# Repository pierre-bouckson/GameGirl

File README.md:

# GameGirl

## Intro
I create this gamegirl for my nieces & for my personnal pleasure

## What

## Game

- pong
- snake
- 2048
- tetris
- rocket
- puissance 4
- casse briques
- demineur
- morpion
- space invaders

## Features

- STM32F429ZIT6
- 2.4" QVGA TFT LCD 
- Joystick
- 2 button 
- 1 start button
- 1 buzzer
- EPROM (see if that neccesary)
- 3D printed case
- Lithium-ion
- USB type C charge 

## Display pipeline

The framebuffer (240×320, RGB565, 150 KB) lives in the external SDRAM at `0xD0000000` (FMC bank 2).

```
          writes                        reads (DMA)
  CPU  ────────────►  SDRAM  ◄────────────  LTDC  ──── parallel RGB ───►  ILI9341
                  (0xD0000000)                        (pixels, ~60 Hz)    (screen)
        via FMC                via FMC
                                            SPI5 ──── config only ─────►  ILI9341
```

- **CPU** draws pixels into the framebuffer in SDRAM, through the FMC.
- **LTDC** has its own DMA: it continuously reads the SDRAM line by line, with no CPU involvement.
- It pushes the pixels to the screen over the **parallel RGB bus** (R/G/B, HSYNC, VSYNC, DOTCLK).
- **ILI9341** just displays what it receives; it never reads memory itself.
- **SPI5** is only used once in `ili9341_Init()` to configure the panel (RGB mode, orientation…). No pixel goes through it.

CPU and LTDC share the FMC bandwidth. The LTDC needs about 9 MB/s (240 × 320 × 2 bytes × 60 Hz) out of ~128 MB/s theoretical (16-bit SDRAM @ 64 MHz), so plenty is left for the CPU.

Because the LTDC reads continuously while the CPU writes into the same buffer, a single buffer can cause tearing. The SDRAM leaves room for double buffering (2 × 150 KB).

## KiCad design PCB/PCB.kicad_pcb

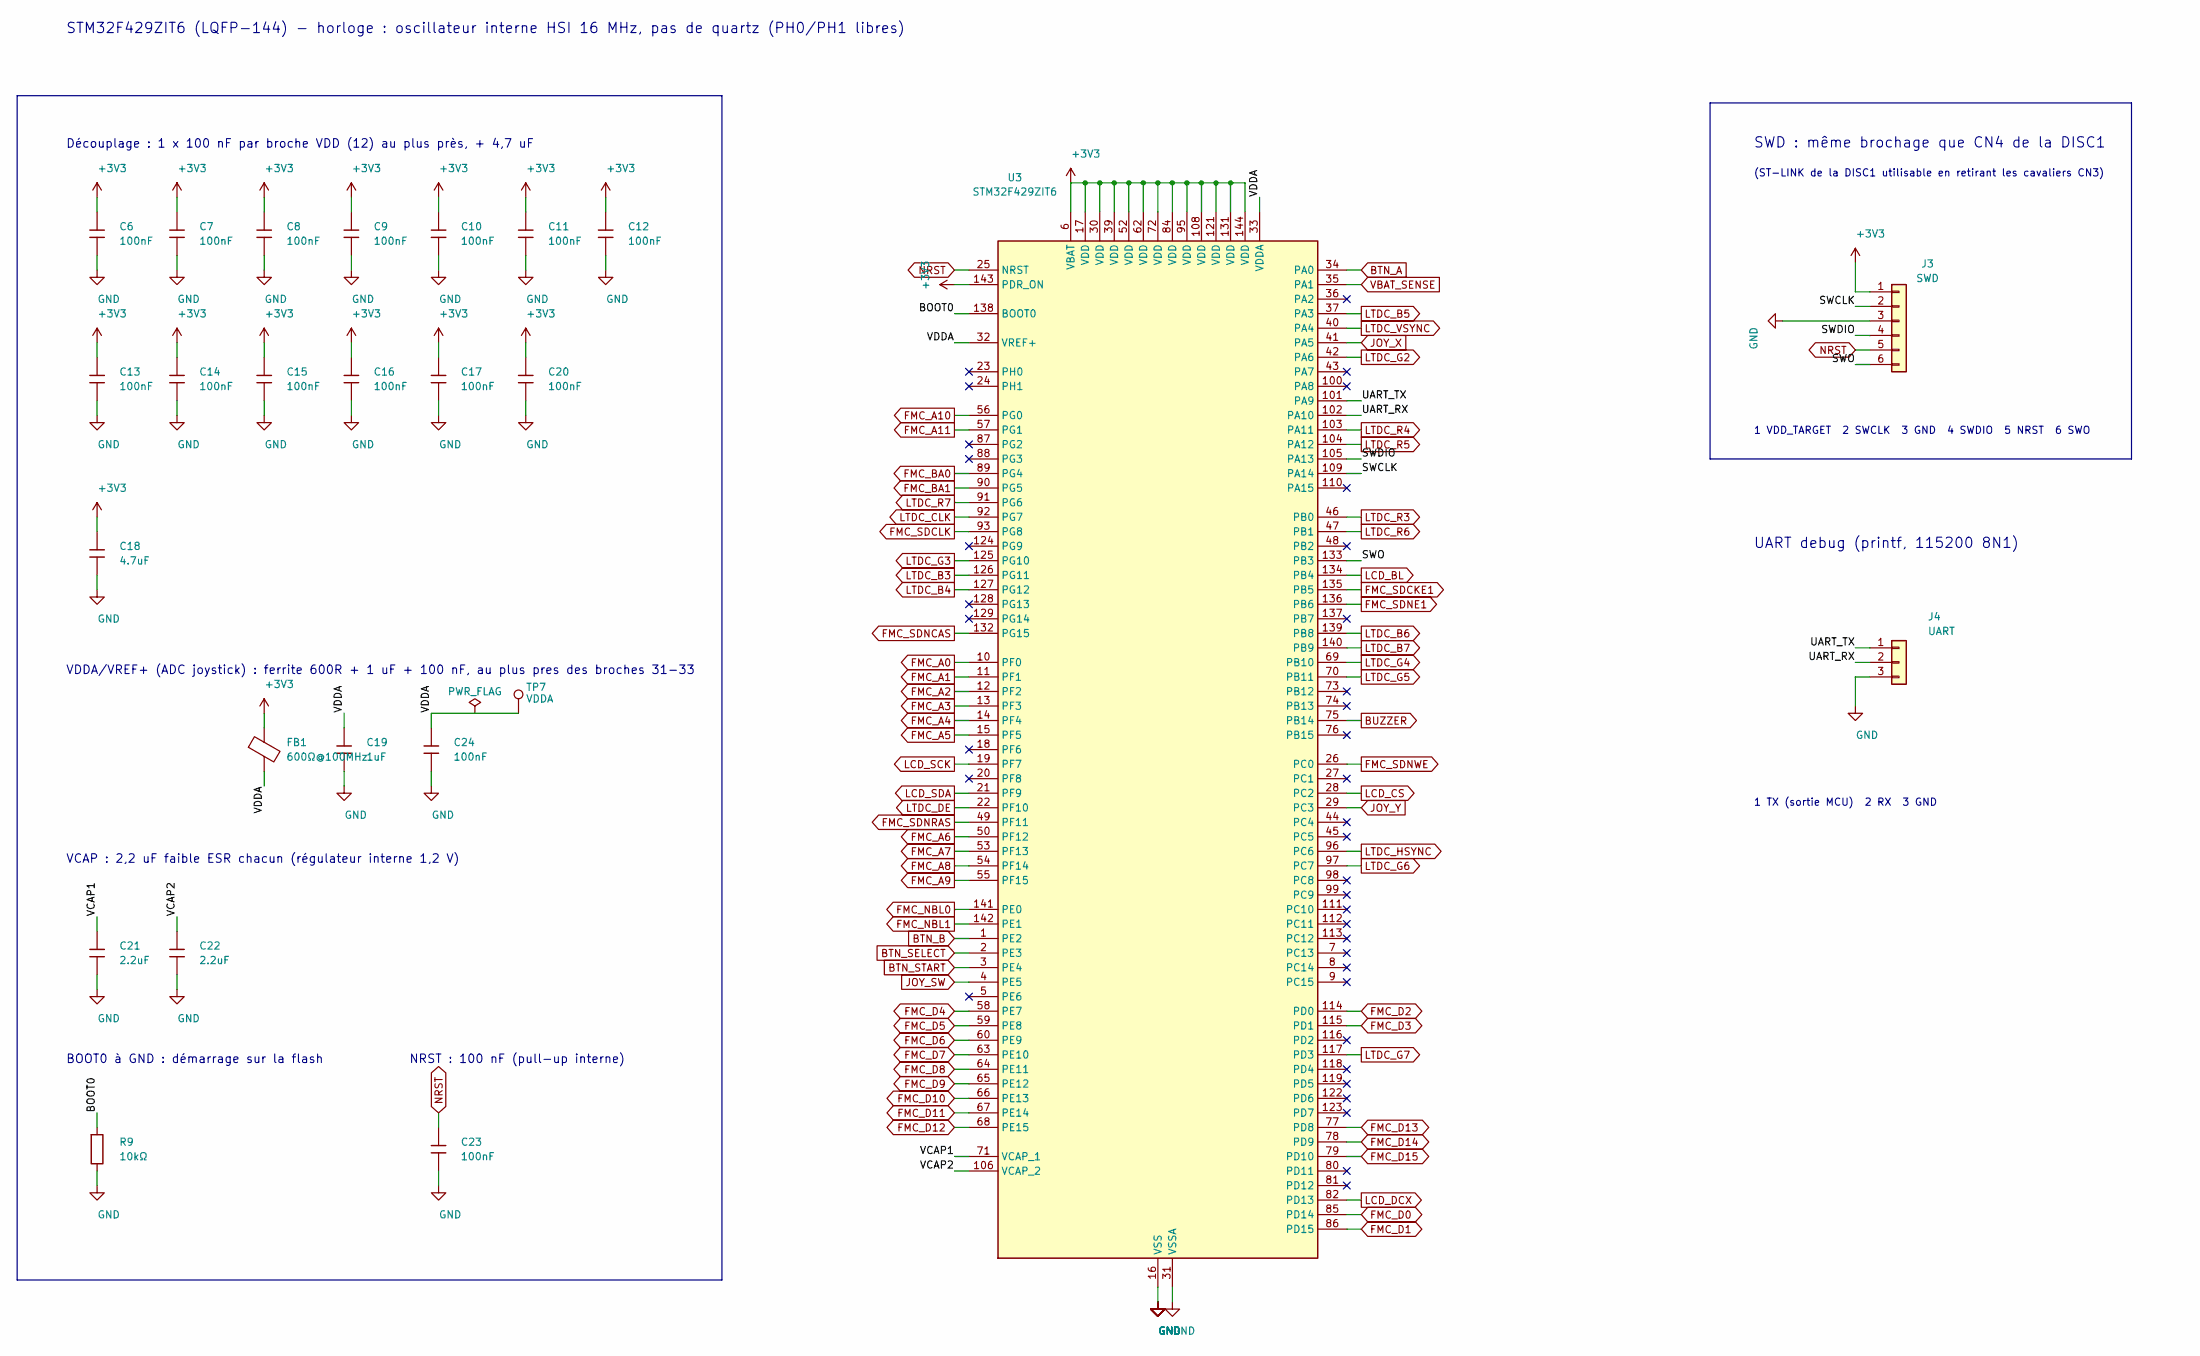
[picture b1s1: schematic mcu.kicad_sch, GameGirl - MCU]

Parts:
C6, C7, C8, C9, C10, C11, C12, C13, C14, C15, C16, C17, C20, C23, C24: 100nF; C_0402; LCSC C1525
C18: 4.7uF; C_0603; LCSC C19666
C19: 1uF; C_0603; LCSC C15849
C21, C22: 2.2uF; C_0603; LCSC C23630
FB1: 600Ω@100MHz; FB_0603; LCSC C1002
J3: SWD; PinHeader_1x06_P2.54mm_Vertical
J4: UART; PinHeader_1x03_P2.54mm_Vertical
R9: 10kΩ; R_0402; LCSC C25744
TP7: VDDA; TestPoint_Pad_D1.5mm
U3: STM32F429ZIT6; LQFP-144_20x20mm_P0.5mm; LCSC C84808

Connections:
+3V3: C6.1, C7.1, C8.1, C9.1, C10.1, C11.1, C12.1, C13.1, C14.1, C15.1, C16.1, C17.1, C18.1, C20.1, FB1.1, J3.1, U3.6 (VBAT), U3.17 (VDD), U3.30 (VDD), U3.39 (VDD), U3.52 (VDD), U3.62 (VDD), U3.72 (VDD), U3.84 (VDD), U3.95 (VDD), U3.108 (VDD), U3.121 (VDD), U3.131 (VDD), U3.143 (PDR_ON), U3.144 (VDD); also elsewhere on the board
/MCU/BOOT0: R9.1, U3.138 (BOOT0)
/MCU/SWCLK: J3.2, U3.109 (PA14)
/MCU/SWDIO: J3.4, U3.105 (PA13)
/MCU/SWO: J3.6, U3.133 (PB3)
/MCU/UART_RX: J4.2, U3.102 (PA10)
/MCU/UART_TX: J4.1, U3.101 (PA9)
/MCU/VCAP1: C21.1, U3.71 (VCAP_1)
/MCU/VCAP2: C22.1, U3.106 (VCAP_2)
/MCU/VDDA: C19.1, C24.1, FB1.2, TP7.1, U3.32 (VREF+), U3.33 (VDDA)
BTN_A: U3.34 (PA0); also elsewhere on the board
BTN_B: U3.1 (PE2); also elsewhere on the board
BTN_SELECT: U3.2 (PE3); also elsewhere on the board
BTN_START: U3.3 (PE4); also elsewhere on the board
BUZZER: U3.75 (PB14); also elsewhere on the board
FMC_A0: U3.10 (PF0); also elsewhere on the board
FMC_A1: U3.11 (PF1); also elsewhere on the board
FMC_A2: U3.12 (PF2); also elsewhere on the board
FMC_A3: U3.13 (PF3); also elsewhere on the board
FMC_A4: U3.14 (PF4); also elsewhere on the board
FMC_A5: U3.15 (PF5); also elsewhere on the board
FMC_A6: U3.50 (PF12); also elsewhere on the board
FMC_A7: U3.53 (PF13); also elsewhere on the board
FMC_A8: U3.54 (PF14); also elsewhere on the board
FMC_A9: U3.55 (PF15); also elsewhere on the board
FMC_A10: U3.56 (PG0); also elsewhere on the board
FMC_A11: U3.57 (PG1); also elsewhere on the board
FMC_BA0: U3.89 (PG4); also elsewhere on the board
FMC_BA1: U3.90 (PG5); also elsewhere on the board
FMC_D0: U3.85 (PD14); also elsewhere on the board
FMC_D1: U3.86 (PD15); also elsewhere on the board
FMC_D2: U3.114 (PD0); also elsewhere on the board
FMC_D3: U3.115 (PD1); also elsewhere on the board
FMC_D4: U3.58 (PE7); also elsewhere on the board
FMC_D5: U3.59 (PE8); also elsewhere on the board
FMC_D6: U3.60 (PE9); also elsewhere on the board
FMC_D7: U3.63 (PE10); also elsewhere on the board
FMC_D8: U3.64 (PE11); also elsewhere on the board
FMC_D9: U3.65 (PE12); also elsewhere on the board
FMC_D10: U3.66 (PE13); also elsewhere on the board
FMC_D11: U3.67 (PE14); also elsewhere on the board
FMC_D12: U3.68 (PE15); also elsewhere on the board
FMC_D13: U3.77 (PD8); also elsewhere on the board
FMC_D14: U3.78 (PD9); also elsewhere on the board
FMC_D15: U3.79 (PD10); also elsewhere on the board
FMC_NBL0: U3.141 (PE0); also elsewhere on the board
FMC_NBL1: U3.142 (PE1); also elsewhere on the board
FMC_SDCKE1: U3.135 (PB5); also elsewhere on the board
FMC_SDCLK: U3.93 (PG8); also elsewhere on the board
FMC_SDNCAS: U3.132 (PG15); also elsewhere on the board
FMC_SDNE1: U3.136 (PB6); also elsewhere on the board
FMC_SDNRAS: U3.49 (PF11); also elsewhere on the board
FMC_SDNWE: U3.26 (PC0); also elsewhere on the board
GND: C6.2, C7.2, C8.2, C9.2, C10.2, C11.2, C12.2, C13.2, C14.2, C15.2, C16.2, C17.2, C18.2, C19.2, C20.2, C21.2, C22.2, C23.2, C24.2, J3.3, J4.3, R9.2, U3.16 (VSS), U3.31 (VSSA), U3.38 (VSS), U3.51 (VSS), U3.61 (VSS), U3.83 (VSS), U3.94 (VSS), U3.107 (VSS), U3.120 (VSS), U3.130 (VSS); also elsewhere on the board
JOY_SW: U3.4 (PE5); also elsewhere on the board
JOY_X: U3.41 (PA5); also elsewhere on the board
JOY_Y: U3.29 (PC3); also elsewhere on the board
LCD_BL: U3.134 (PB4); also elsewhere on the board
LCD_CS: U3.28 (PC2); also elsewhere on the board
LCD_DCX: U3.82 (PD13); also elsewhere on the board
LCD_SCK: U3.19 (PF7); also elsewhere on the board
LCD_SDA: U3.21 (PF9); also elsewhere on the board
LTDC_B3: U3.126 (PG11); also elsewhere on the board
LTDC_B4: U3.127 (PG12); also elsewhere on the board
LTDC_B5: U3.37 (PA3); also elsewhere on the board
LTDC_B6: U3.139 (PB8); also elsewhere on the board
LTDC_B7: U3.140 (PB9); also elsewhere on the board
LTDC_CLK: U3.92 (PG7); also elsewhere on the board
LTDC_DE: U3.22 (PF10); also elsewhere on the board
LTDC_G2: U3.42 (PA6); also elsewhere on the board
LTDC_G3: U3.125 (PG10); also elsewhere on the board
LTDC_G4: U3.69 (PB10); also elsewhere on the board
LTDC_G5: U3.70 (PB11); also elsewhere on the board
LTDC_G6: U3.97 (PC7); also elsewhere on the board
LTDC_G7: U3.117 (PD3); also elsewhere on the board
LTDC_HSYNC: U3.96 (PC6); also elsewhere on the board
LTDC_R3: U3.46 (PB0); also elsewhere on the board
LTDC_R4: U3.103 (PA11); also elsewhere on the board
LTDC_R5: U3.104 (PA12); also elsewhere on the board
LTDC_R6: U3.47 (PB1); also elsewhere on the board
LTDC_R7: U3.91 (PG6); also elsewhere on the board
LTDC_VSYNC: U3.40 (PA4); also elsewhere on the board
NRST: C23.1, J3.5, U3.25 (NRST); also elsewhere on the board
VBAT_SENSE: U3.35 (PA1); also elsewhere on the board

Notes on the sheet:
(ST-LINK de la DISC1 utilisable en retirant les cavaliers CN3)
BOOT0 à GND : démarrage sur la flash
1 VDD_TARGET 2 SWCLK 3 GND 4 SWDIO 5 NRST 6 SWO
VDDA/VREF+ (ADC joystick) : ferrite 600R + 1 uF + 100 nF, au plus pres des broches 31-33
SWD : même brochage que CN4 de la DISC1
NRST : 100 nF (pull-up interne)
Découplage : 1 x 100 nF par broche VDD (12) au plus près, + 4,7 uF
1 TX (sortie MCU) 2 RX 3 GND
VCAP : 2,2 uF faible ESR chacun (régulateur interne 1,2 V)
UART debug (printf, 115200 8N1)
STM32F429ZIT6 (LQFP-144) - horloge : oscillateur interne HSI 16 MHz, pas de quartz (PH0/PH1 libres)

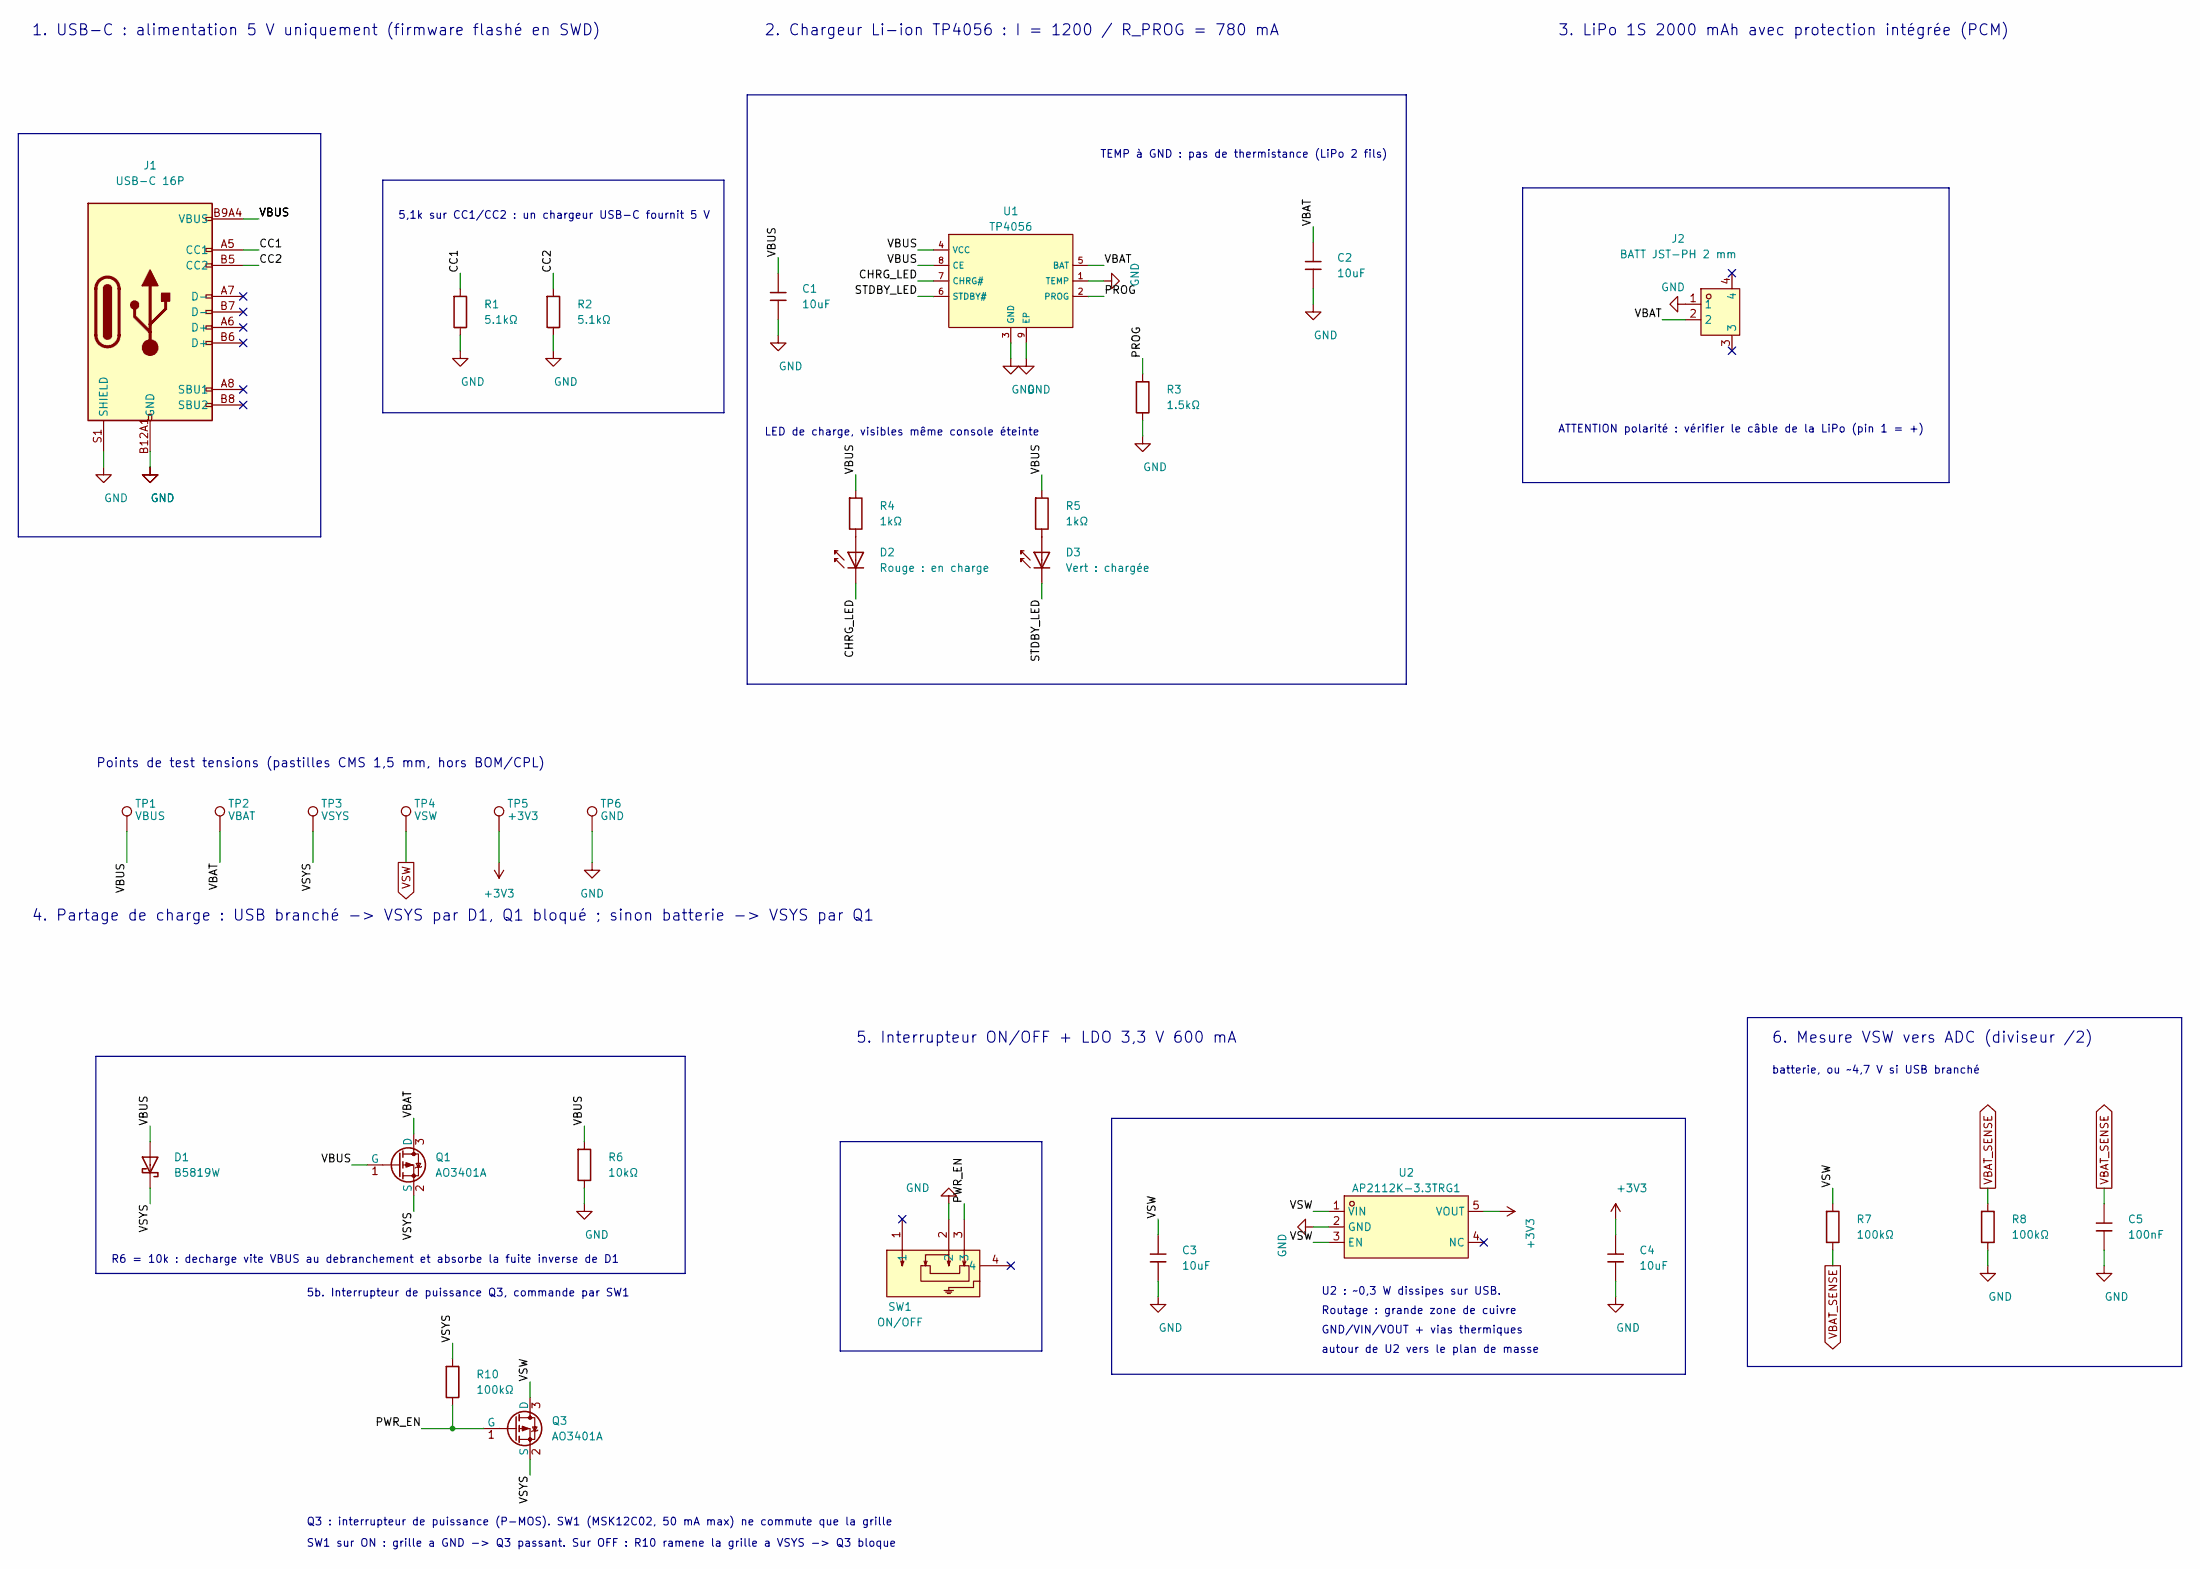
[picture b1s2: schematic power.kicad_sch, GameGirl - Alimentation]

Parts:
C1, C2, C3, C4: 10uF; C_0603; LCSC C19702
C5: 100nF; C_0402; LCSC C1525
D1: B5819W; D_SOD-123; LCSC C64885
D2: Rouge : en charge; D_0603; LCSC C2286
D3: Vert : chargée; D_0805; LCSC C2297
J1: USB-C 16P; TYPE-C-SMD_HX-TYPE-C-16PIN; LCSC C2927039
J2: BATT JST-PH 2 mm; CONN-SMD_P2.00_S2B-PH-SM4-TB-LF-SN; LCSC C295747
Q1, Q3: AO3401A; Q_SOT-23; LCSC C15127
R1, R2: 5.1kΩ; R_0402; LCSC C25905
R3: 1.5kΩ; R_0402; LCSC C25867
R4, R5: 1kΩ; R_0402; LCSC C11702
R6: 10kΩ; R_0402; LCSC C25744
R7, R8, R10: 100kΩ; R_0402; LCSC C25741
SW1: ON/OFF; SW-TH_MSK12C02; LCSC C431540
TP1: VBUS; TestPoint_Pad_D1.5mm
TP2: VBAT; TestPoint_Pad_D1.5mm
TP3: VSYS; TestPoint_Pad_D1.5mm
TP4: VSW; TestPoint_Pad_D1.5mm
TP5: +3V3; TestPoint_Pad_D1.5mm
TP6: GND; TestPoint_Pad_D1.5mm
U1: TP4056; ESOP-8_L4.9-W3.9-P1.27-LS6.0-BL-EP; LCSC C16581
U2: AP2112K-3.3TRG1; SOT-25-5_L2.9-W1.6-P0.95-LS2.8-BL; LCSC C51118

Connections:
+3V3: C4.1, TP5.1, U2.5 (VOUT); also elsewhere on the board
/Alimentation/CC1: J1.A5 (CC1), R1.1
/Alimentation/CC2: J1.B5 (CC2), R2.1
/Alimentation/CHRG_LED: D2.1, U1.7 (CHRG#)
/Alimentation/PROG: R3.1, U1.2 (PROG)
/Alimentation/PWR_EN: Q3.1 (G), R10.2, SW1.3
/Alimentation/STDBY_LED: D3.1, U1.6 (STDBY#)
/Alimentation/VBAT: C2.1, J2.2, Q1.3 (D), TP2.1, U1.5 (BAT)
/Alimentation/VBUS: C1.1, D1.2, J1.A9B4 (VBUS), J1.B9A4 (VBUS), Q1.1 (G), R4.1, R5.1, R6.1, TP1.1, U1.4 (VCC), U1.8 (CE)
/Alimentation/VSYS: D1.1, Q1.2 (S), Q3.2 (S), R10.1, TP3.1
GND: C1.2, C2.2, C3.2, C4.2, C5.2, J1.A12B1 (GND), J1.B12A1 (GND), J1.S1 (SHIELD), J2.1, R1.2, R2.2, R3.2, R6.2, R8.2, SW1.2, TP6.1, U1.1 (TEMP), U1.3 (GND), U1.9 (EP), U2.2 (GND); also elsewhere on the board
unnamed: D2.2, R4.2
unnamed: D3.2, R5.2
VBAT_SENSE: C5.1, R7.2, R8.1; also elsewhere on the board
VSW: C3.1, Q3.3 (D), R7.1, TP4.1, U2.1 (VIN), U2.3 (EN); also elsewhere on the board

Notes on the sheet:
3. LiPo 1S 2000 mAh avec protection intégrée (PCM)
5. Interrupteur ON/OFF + LDO 3,3 V 600 mA
Q3 : interrupteur de puissance (P-MOS). SW1 (MSK12C02, 50 mA max) ne commute que la grille
TEMP à GND : pas de thermistance (LiPo 2 fils)
Routage : grande zone de cuivre
ATTENTION polarité : vérifier le câble de la LiPo (pin 1 = +)
5b. Interrupteur de puissance Q3, commande par SW1
GND/VIN/VOUT + vias thermiques
4. Partage de charge : USB branché -> VSYS par D1, Q1 bloqué ; sinon batterie -> VSYS par Q1
5,1k sur CC1/CC2 : un chargeur USB-C fournit 5 V
autour de U2 vers le plan de masse
SW1 sur ON : grille a GND -> Q3 passant. Sur OFF : R10 ramene la grille a VSYS -> Q3 bloque
1. USB-C : alimentation 5 V uniquement (firmware flashé en SWD)
LED de charge, visibles même console éteinte
Points de test tensions (pastilles CMS 1,5 mm, hors BOM/CPL)
batterie, ou ~4,7 V si USB branché
R6 = 10k : decharge vite VBUS au debranchement et absorbe la fuite inverse de D1
U2 : ~0,3 W dissipes sur USB.
6. Mesure VSW vers ADC (diviseur /2)
2. Chargeur Li-ion TP4056 : I = 1200 / R_PROG = 780 mA

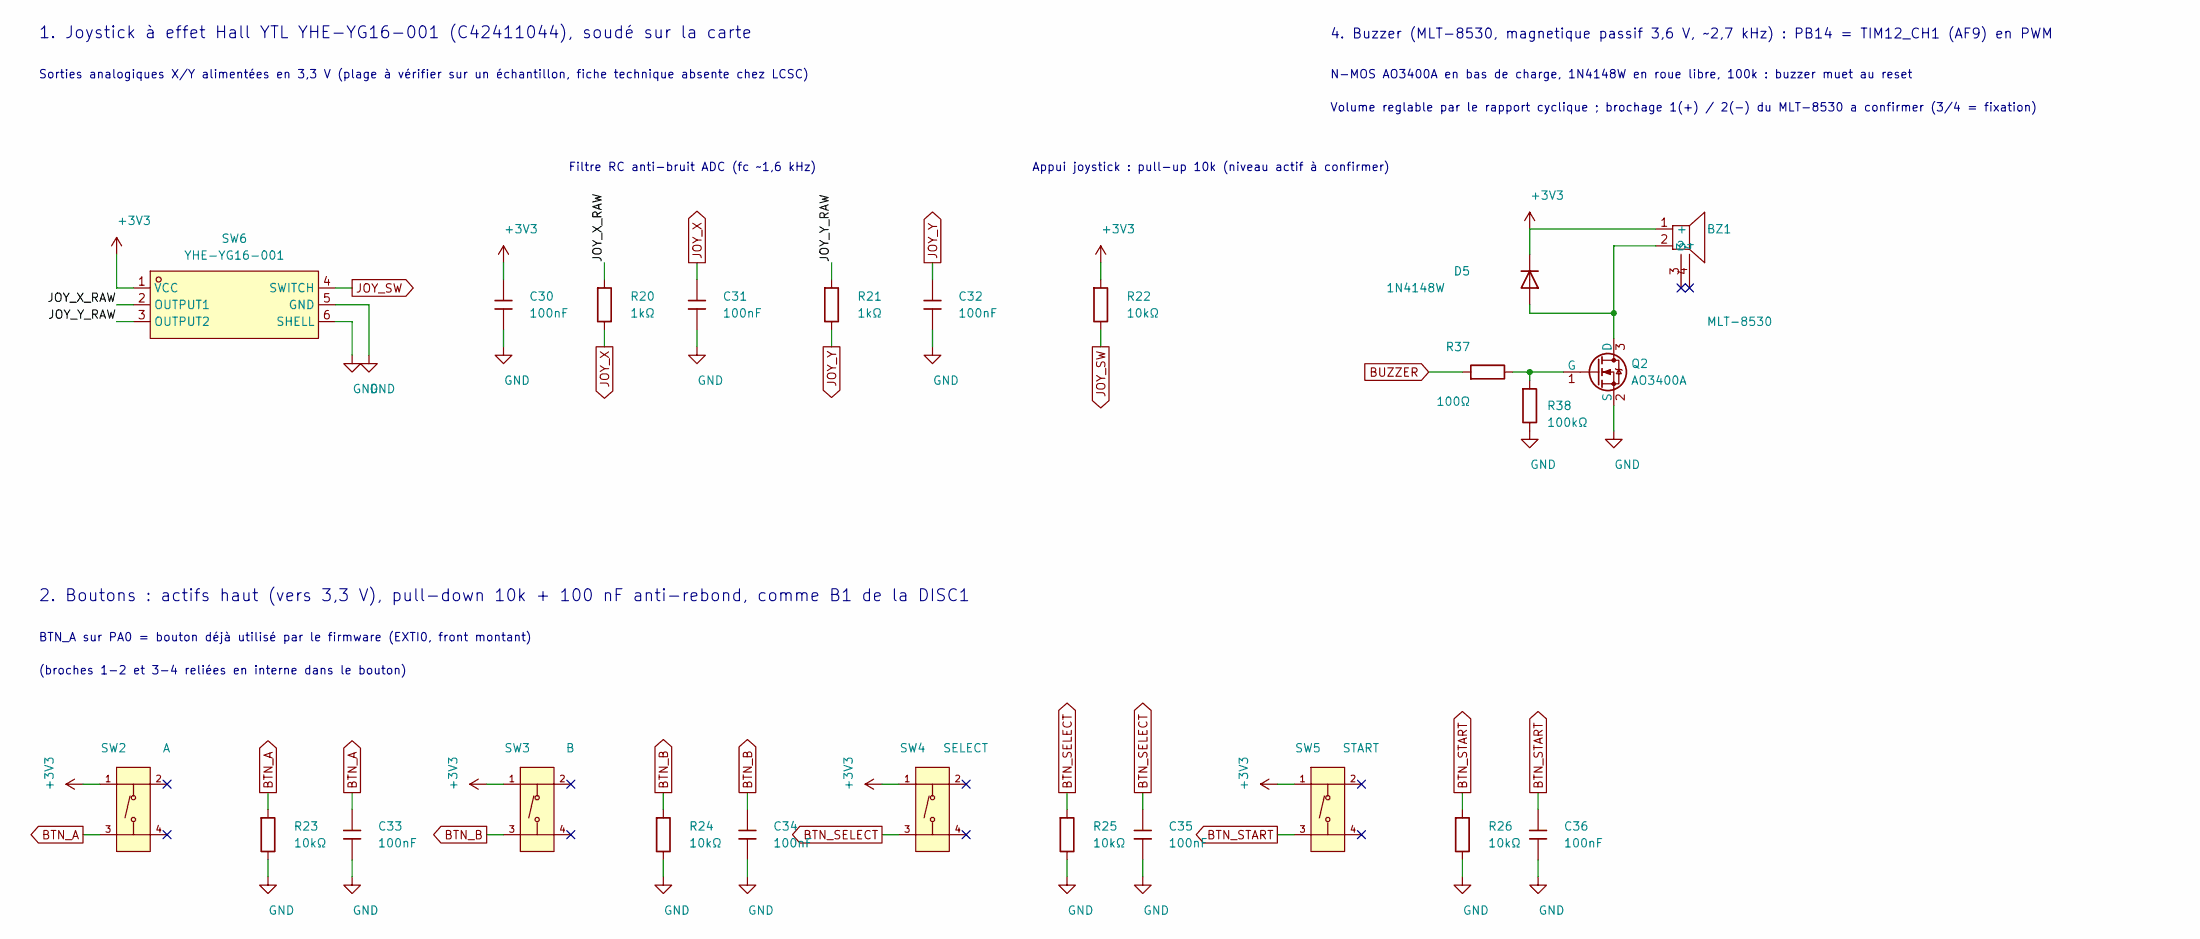
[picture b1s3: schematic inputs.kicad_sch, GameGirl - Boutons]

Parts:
BZ1: MLT-8530; BUZ-SMD_4P-L8.5-W8.5-P8.50-BR; LCSC C94599
C30, C31, C32, C33, C34, C35, C36: 100nF; C_0402; LCSC C1525
D5: 1N4148W; D_SOD-123; LCSC C81598
Q2: AO3400A; Q_SOT-23; LCSC C20917
R20, R21: 1kΩ; R_0402; LCSC C11702
R22, R23, R24, R25, R26: 10kΩ; R_0402; LCSC C25744
R37: 100Ω; R_0402; LCSC C25076
R38: 100kΩ; R_0402; LCSC C25741
SW2: A; SW-SMD_4P-L5.1-W5.1-P3.70-LS6.5-TL-2; LCSC C318884
SW3: B; SW-SMD_4P-L5.1-W5.1-P3.70-LS6.5-TL-2; LCSC C318884
SW4: SELECT; SW-SMD_4P-L5.1-W5.1-P3.70-LS6.5-TL-2; LCSC C318884
SW5: START; SW-SMD_4P-L5.1-W5.1-P3.70-LS6.5-TL-2; LCSC C318884
SW6: YHE-YG16-001; SW-TH_YHE-YG16-001-SH1B166A1; LCSC C42411044

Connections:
+3V3: BZ1.1 (+), C30.1, D5.1, R22.1, SW2.1 (A), SW3.1 (A), SW4.1 (A), SW5.1 (A), SW6.1 (VCC); also elsewhere on the board
/Boutons/JOY_X_RAW: R20.1, SW6.2 (OUTPUT1)
/Boutons/JOY_Y_RAW: R21.1, SW6.3 (OUTPUT2)
BTN_A: C33.1, R23.1, SW2.3 (C); also elsewhere on the board
BTN_B: C34.1, R24.1, SW3.3 (C); also elsewhere on the board
BTN_SELECT: C35.1, R25.1, SW4.3 (C); also elsewhere on the board
BTN_START: C36.1, R26.1, SW5.3 (C); also elsewhere on the board
BUZZER: R37.1; also elsewhere on the board
GND: C30.2, C31.2, C32.2, C33.2, C34.2, C35.2, C36.2, Q2.2 (S), R23.2, R24.2, R25.2, R26.2, R38.2, SW6.5 (GND), SW6.6 (SHELL); also elsewhere on the board
JOY_SW: R22.2, SW6.4 (SWITCH); also elsewhere on the board
JOY_X: C31.1, R20.2; also elsewhere on the board
JOY_Y: C32.1, R21.2; also elsewhere on the board
unnamed: BZ1.2, D5.2, Q2.3 (D)
unnamed: Q2.1 (G), R37.2, R38.1

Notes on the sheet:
4. Buzzer (MLT-8530, magnetique passif 3,6 V, ~2,7 kHz) : PB14 = TIM12_CH1 (AF9) en PWM
2. Boutons : actifs haut (vers 3,3 V), pull-down 10k + 100 nF anti-rebond, comme B1 de la DISC1
Volume reglable par le rapport cyclique ; brochage 1(+) / 2(-) du MLT-8530 a confirmer (3/4 = fixation)
1. Joystick à effet Hall YTL YHE-YG16-001 (C42411044), soudé sur la carte
(broches 1-2 et 3-4 reliées en interne dans le bouton)
Sorties analogiques X/Y alimentées en 3,3 V (plage à vérifier sur un échantillon, fiche technique absente chez LCSC)
BTN_A sur PA0 = bouton déjà utilisé par le firmware (EXTI0, front montant)
Appui joystick : pull-up 10k (niveau actif à confirmer)
Filtre RC anti-bruit ADC (fc ~1,6 kHz)
N-MOS AO3400A en bas de charge, 1N4148W en roue libre, 100k : buzzer muet au reset

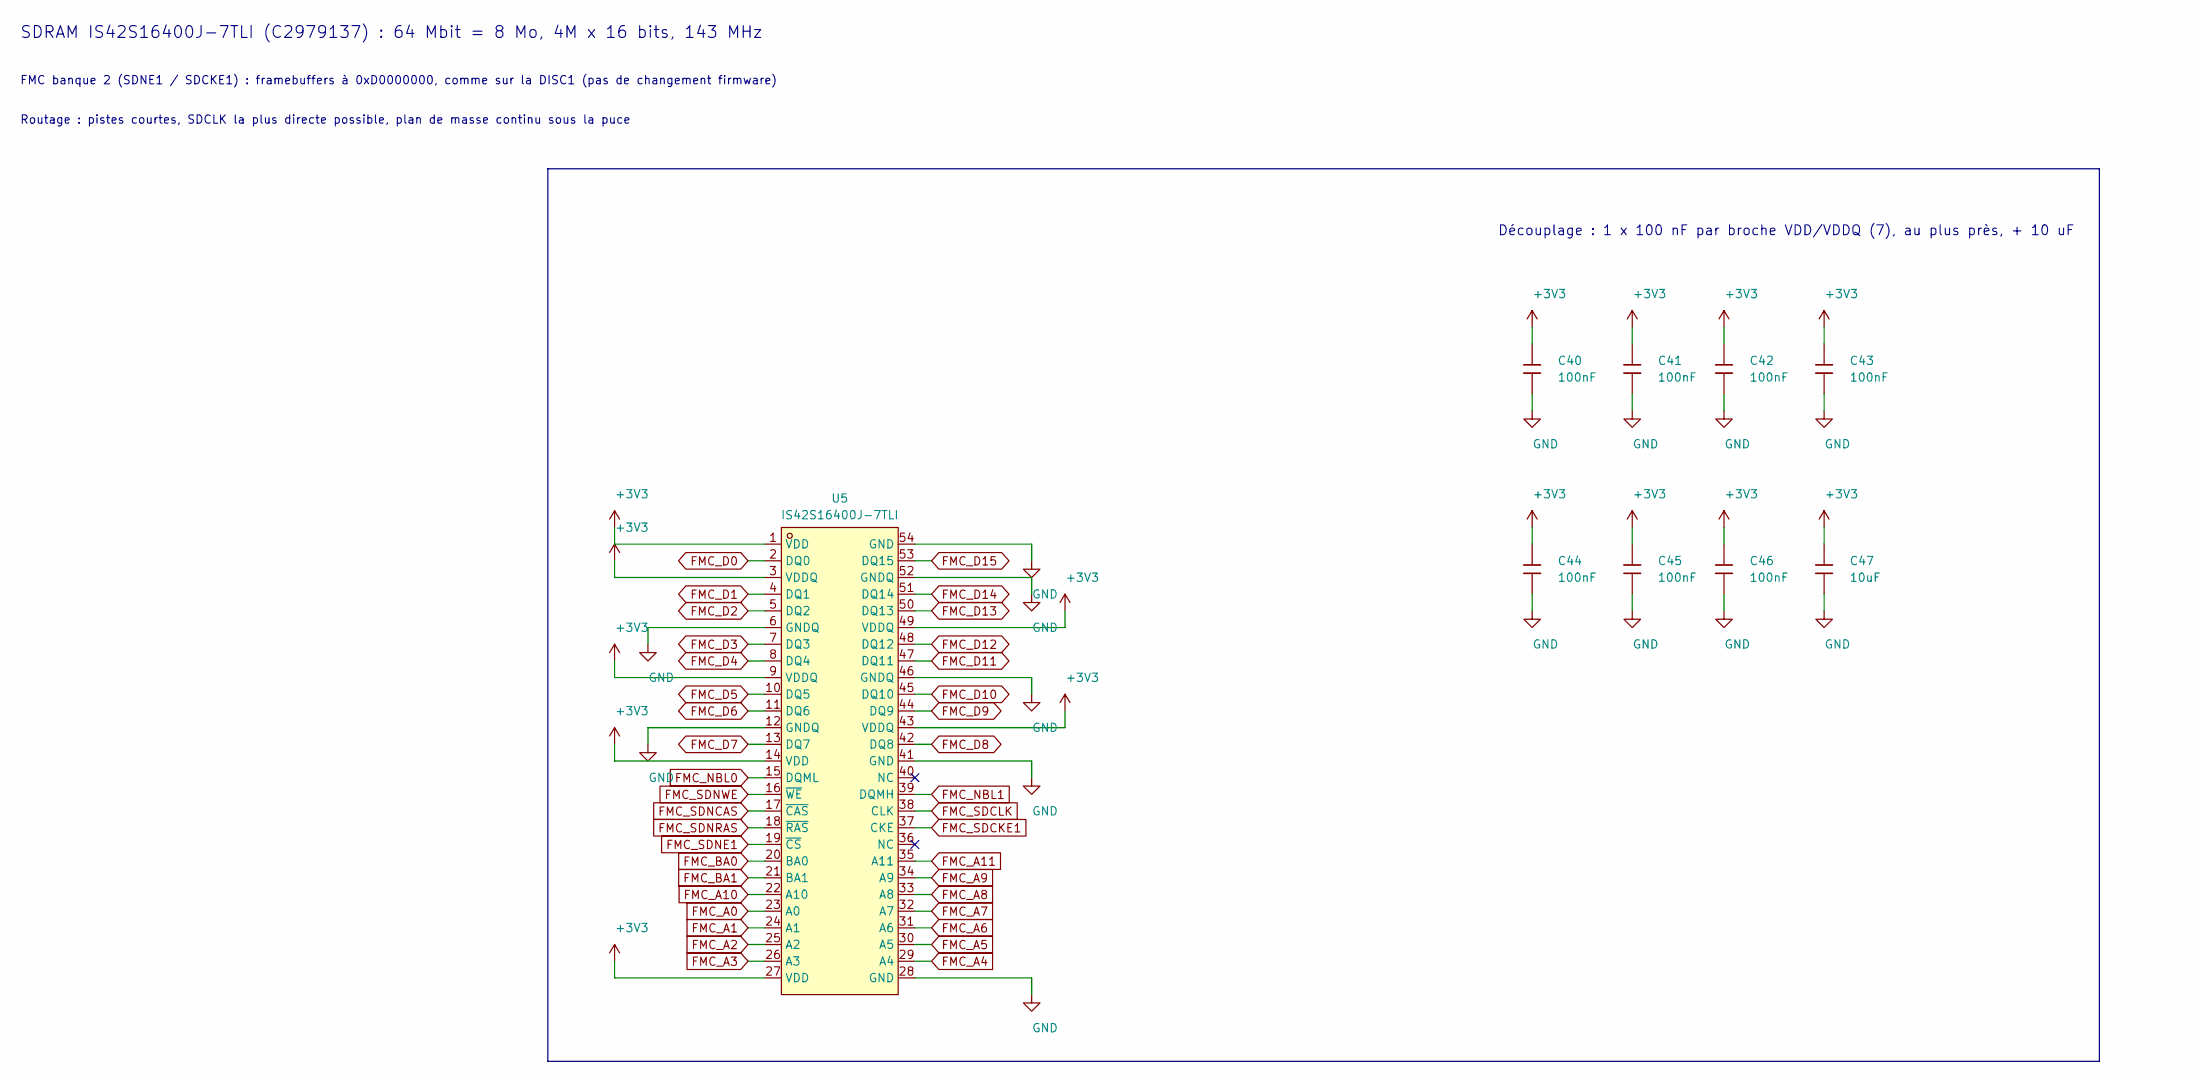
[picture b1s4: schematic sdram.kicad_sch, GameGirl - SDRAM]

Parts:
C40, C41, C42, C43, C44, C45, C46: 100nF; C_0402; LCSC C1525
C47: 10uF; C_0603; LCSC C19702
U5: IS42S16400J-7TLI; TSOP-54_L22.2-W10.2-P0.80-LS11.8-BL; LCSC C2979137

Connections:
+3V3: C40.1, C41.1, C42.1, C43.1, C44.1, C45.1, C46.1, C47.1, U5.1 (VDD), U5.3 (VDDQ), U5.9 (VDDQ), U5.14 (VDD), U5.27 (VDD), U5.43 (VDDQ), U5.49 (VDDQ); also elsewhere on the board
FMC_A0: U5.23 (A0); also elsewhere on the board
FMC_A1: U5.24 (A1); also elsewhere on the board
FMC_A2: U5.25 (A2); also elsewhere on the board
FMC_A3: U5.26 (A3); also elsewhere on the board
FMC_A4: U5.29 (A4); also elsewhere on the board
FMC_A5: U5.30 (A5); also elsewhere on the board
FMC_A6: U5.31 (A6); also elsewhere on the board
FMC_A7: U5.32 (A7); also elsewhere on the board
FMC_A8: U5.33 (A8); also elsewhere on the board
FMC_A9: U5.34 (A9); also elsewhere on the board
FMC_A10: U5.22 (A10); also elsewhere on the board
FMC_A11: U5.35 (A11); also elsewhere on the board
FMC_BA0: U5.20 (BA0); also elsewhere on the board
FMC_BA1: U5.21 (BA1); also elsewhere on the board
FMC_D0: U5.2 (DQ0); also elsewhere on the board
FMC_D1: U5.4 (DQ1); also elsewhere on the board
FMC_D2: U5.5 (DQ2); also elsewhere on the board
FMC_D3: U5.7 (DQ3); also elsewhere on the board
FMC_D4: U5.8 (DQ4); also elsewhere on the board
FMC_D5: U5.10 (DQ5); also elsewhere on the board
FMC_D6: U5.11 (DQ6); also elsewhere on the board
FMC_D7: U5.13 (DQ7); also elsewhere on the board
FMC_D8: U5.42 (DQ8); also elsewhere on the board
FMC_D9: U5.44 (DQ9); also elsewhere on the board
FMC_D10: U5.45 (DQ10); also elsewhere on the board
FMC_D11: U5.47 (DQ11); also elsewhere on the board
FMC_D12: U5.48 (DQ12); also elsewhere on the board
FMC_D13: U5.50 (DQ13); also elsewhere on the board
FMC_D14: U5.51 (DQ14); also elsewhere on the board
FMC_D15: U5.53 (DQ15); also elsewhere on the board
FMC_NBL0: U5.15 (DQML); also elsewhere on the board
FMC_NBL1: U5.39 (DQMH); also elsewhere on the board
FMC_SDCKE1: U5.37 (CKE); also elsewhere on the board
FMC_SDCLK: U5.38 (CLK); also elsewhere on the board
FMC_SDNCAS: U5.17 (~CAS); also elsewhere on the board
FMC_SDNE1: U5.19 (~CS); also elsewhere on the board
FMC_SDNRAS: U5.18 (~RAS); also elsewhere on the board
FMC_SDNWE: U5.16 (~WE); also elsewhere on the board
GND: C40.2, C41.2, C42.2, C43.2, C44.2, C45.2, C46.2, C47.2, U5.6 (GNDQ), U5.12 (GNDQ), U5.28 (GND), U5.41 (GND), U5.46 (GNDQ), U5.52 (GNDQ), U5.54 (GND); also elsewhere on the board

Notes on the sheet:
Routage : pistes courtes, SDCLK la plus directe possible, plan de masse continu sous la puce
SDRAM IS42S16400J-7TLI (C2979137) : 64 Mbit = 8 Mo, 4M x 16 bits, 143 MHz
Découplage : 1 x 100 nF par broche VDD/VDDQ (7), au plus près, + 10 uF
FMC banque 2 (SDNE1 / SDCKE1) : framebuffers à 0xD0000000, comme sur la DISC1 (pas de changement firmware)
